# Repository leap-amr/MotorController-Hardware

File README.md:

# MotorController-Hardware
モータドライバのハードウェア設計のためのリポジトリ

# Image

# Development Software Versions
Application: KiCad x64 on x64

Version: 7.0.6, release build

Libraries:
    wxWidgets 3.2.2
    FreeType 2.12.1
    HarfBuzz 6.0.0
    FontConfig 2.14.1
    libcurl/7.88.1-DEV Schannel zlib/1.2.13

Platform: Windows 10 (build 19045), 64-bit edition, 64 bit, Little endian, wxMSW

    Build Info:
    Date: Jul  6 2023 04:56:45
    wxWidgets: 3.2.2 (wchar_t,wx containers)
    Boost: 1.81.0
    OCC: 7.6.3
    Curl: 7.88.1-DEV
    ngspice: 40
    Compiler: Visual C++ 1936 without C++ ABI

Build settings:
    KICAD_SPICE=ON

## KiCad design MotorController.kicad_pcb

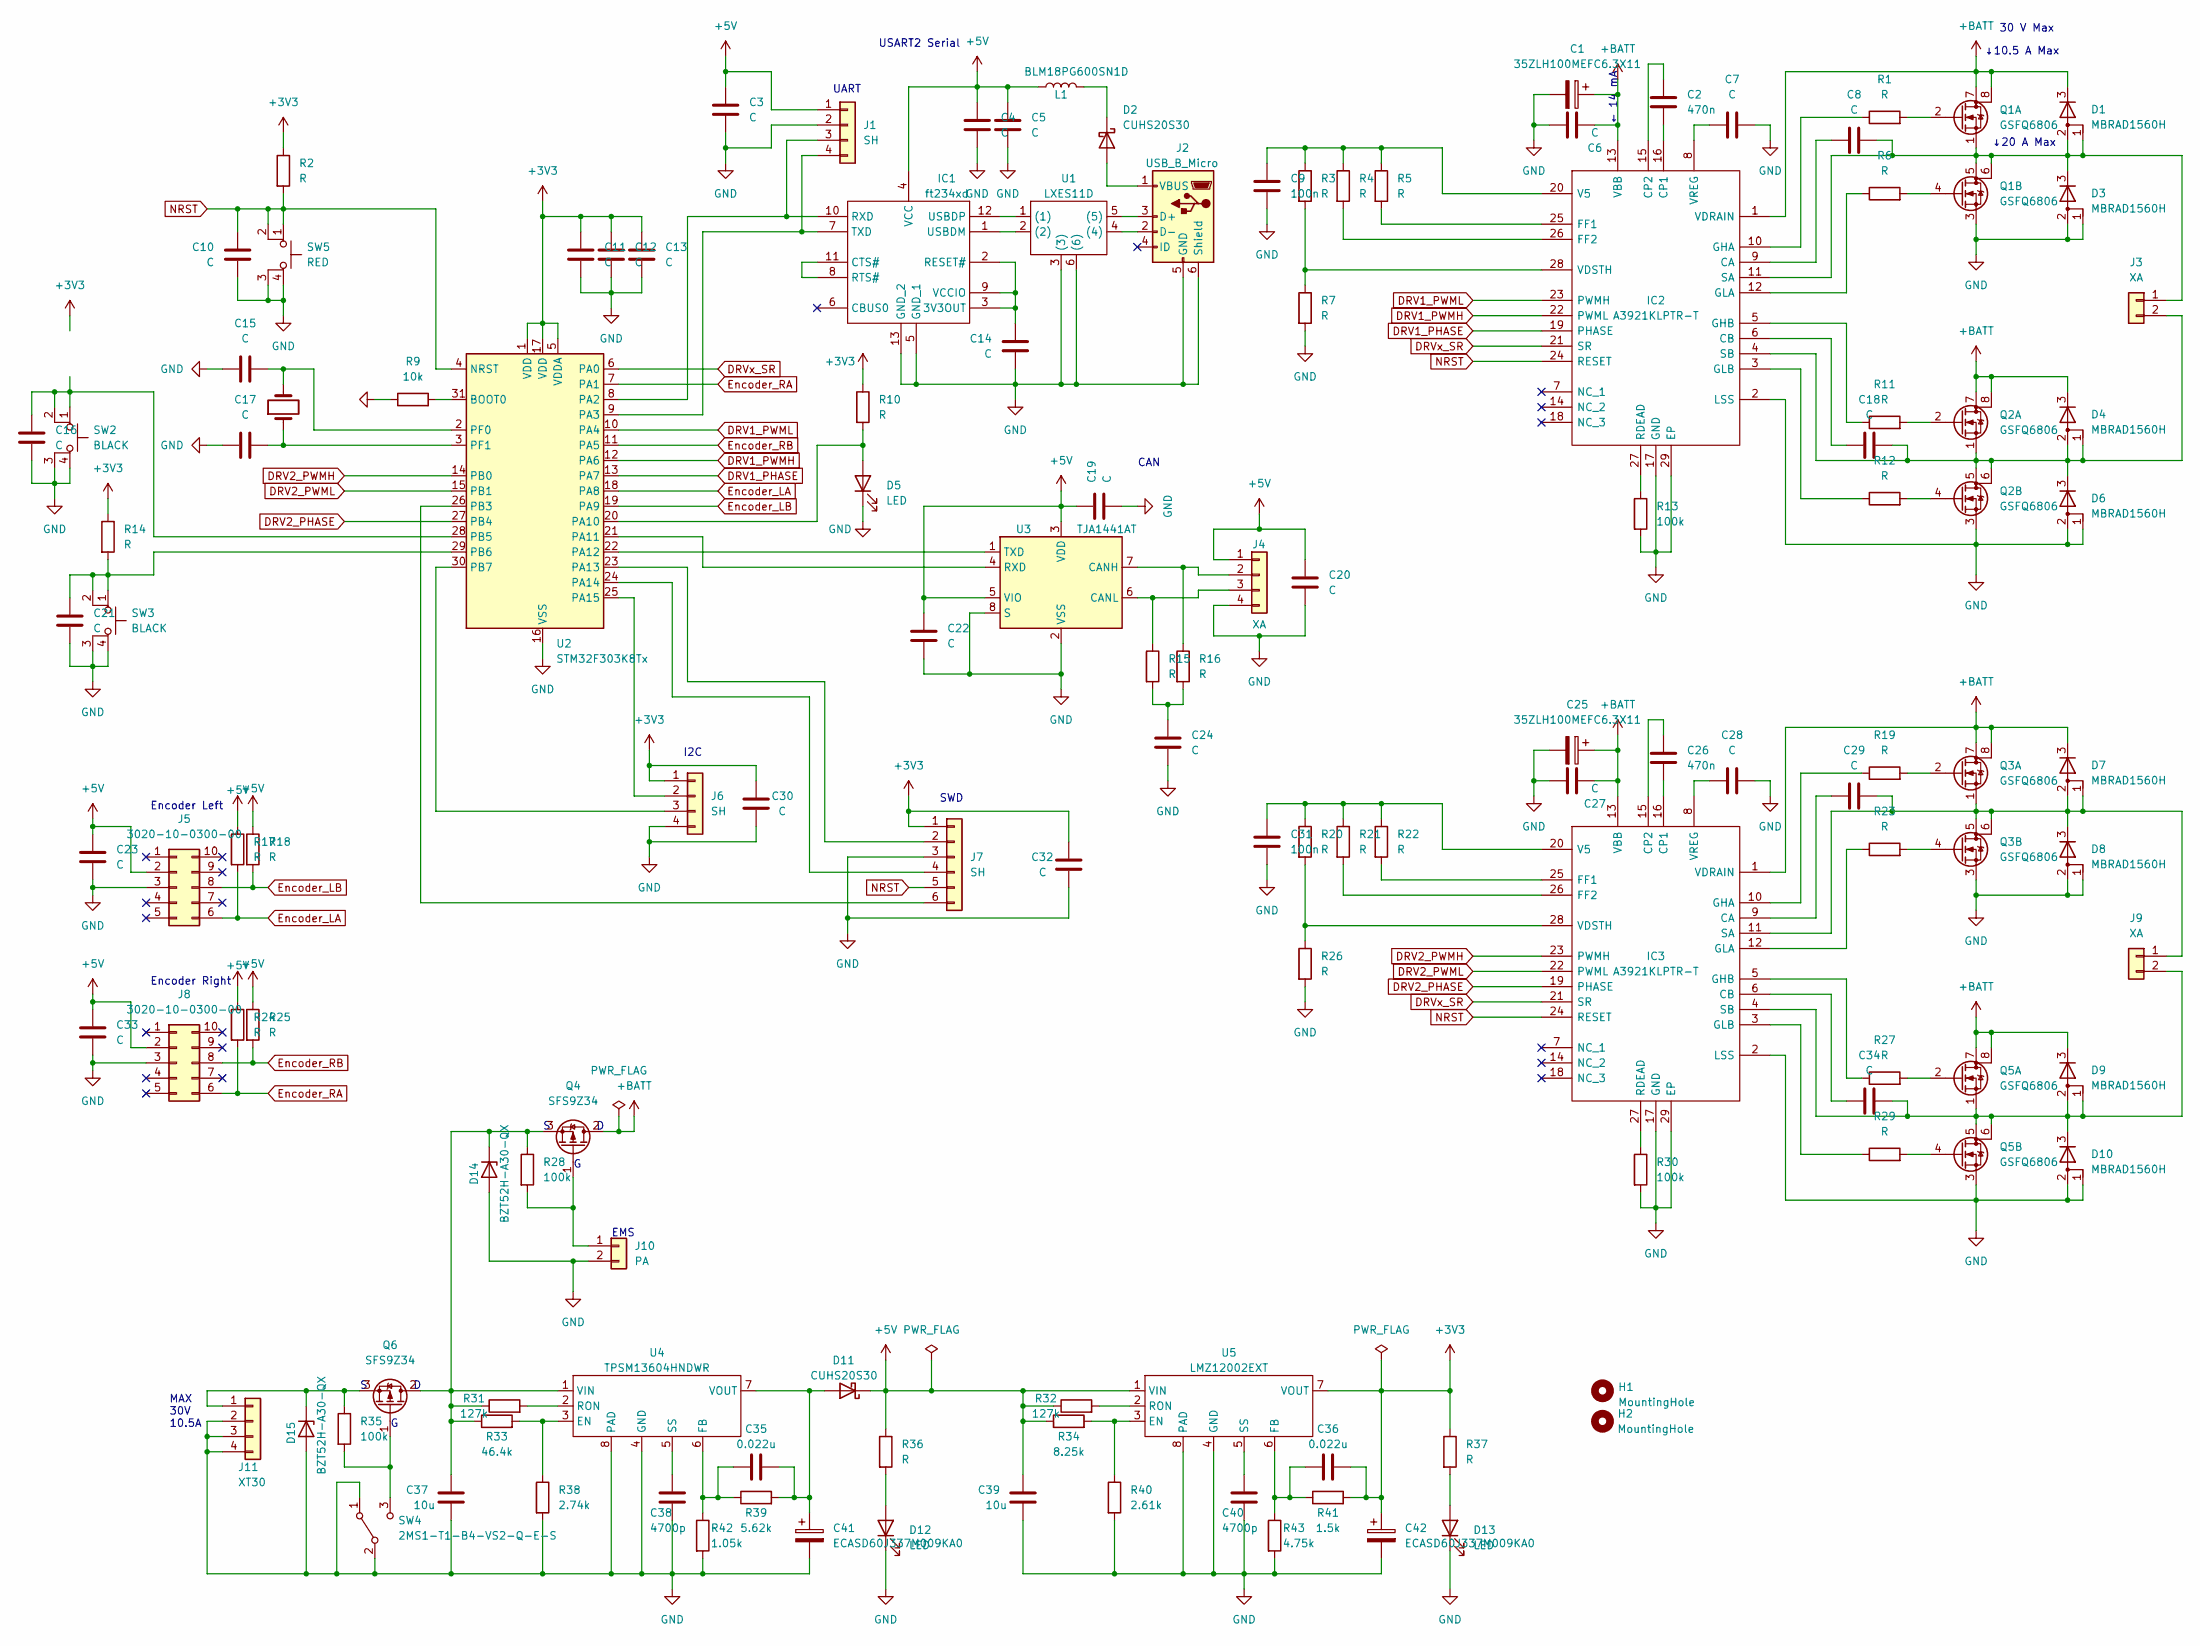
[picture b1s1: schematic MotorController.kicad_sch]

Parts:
C1, C25: 35ZLH100MEFC6.3X11; CP_Radial_D6.3mm_P2.50mm
C2, C26: 470n; C_0603_1608Metric
C3, C4, C5, C6, C7, C8, C10, C11, C12, C13, C14, C15, C16, C17, C18, C19, C20, C21, C22, C23, C24, C27, C28, C29, C30, C32, C33, C34: C; C_0603_1608Metric
C9, C31: 100n; C_0603_1608Metric
C35, C36: 0.022u; C_0603_1608Metric
C37, C39: 10u; C_0603_1608Metric
C38, C40: 4700p; C_0603_1608Metric
C41, C42: ECASD60J337M009KA0; CAPPM7343X310N
D1, D3, D4, D6, D7, D8, D9, D10: MBRAD1560H; DIO_MBRAD1560H
D2, D11: CUHS20S30; CUHS20S40H3F
D5, D12, D13: LED; LED_0603_1608Metric
D14, D15: BZT52H-A30-QX; D_1206_3216Metric
H1, H2: MountingHole; MountingHole_3.2mm_M3
IC1: ft234xd; SON45P300X300X80-13N-D; Manufacturer_Part_Number ft234xd
IC2, IC3: A3921KLPTR-T; A3944KLPTRT; Manufacturer_Part_Number A3921KLPTR-T; Mouser Part Number 250-A3921KLPTR-T
J1, J6: SH; JST_SH_BM04B-SRSS-TB_1x04-1MP_P1.00mm_Vertical
J2: USB_B_Micro; USB_Micro-B_Amphenol_10118194_Horizontal
J3, J9: XA; JST_XA_B02B-XASK-1-A_1x02_P2.50mm_Vertical
J4: XA; JST_XA_B04B-XASK-1-A_1x04_P2.50mm_Vertical
J5, J8: 3020-10-0300-00; IDC-Header_2x05_P2.54mm_Vertical
J7: SH; JST_SH_BM06B-SRSS-TB_1x06-1MP_P1.00mm_Vertical
J10: PA; PA_01x02
J11: XT30; XT30PWM
L1: BLM18PG600SN1D; L_0603_1608Metric
Q1, Q2, Q3, Q5: GSFQ6806; SO-8_3.9x4.9mm_P1.27mm
Q4, Q6: SFS9Z34; TO-220F-3_Horizontal_TabDown
R1, R2, R3, R4, R5, R6, R7, R10, R11, R12, R14, R15, R16, R17, R18, R19, R20, R21, R22, R23, R24, R25, R26, R27, R29, R36, R37: R; R_0603_1608Metric
R9: 10k; R_0603_1608Metric
R13, R28, R30, R35: 100k; R_0603_1608Metric
R31, R32: 127k; R_0603_1608Metric
R33: 46.4k; R_0603_1608Metric
R34: 8.25k; R_0603_1608Metric
R38: 2.74k; R_0603_1608Metric
R39: 5.62k; R_0603_1608Metric
R40: 2.61k; R_0603_1608Metric
R41: 1.5k; R_0603_1608Metric
R42: 1.05k; R_0603_1608Metric
R43: 4.75k; R_0603_1608Metric
SW2, SW3: BLACK; DTS-63-N-V-BLK(TS-0606-F-N
SW4: 2MS1-T1-B4-VS2-Q-E-S
SW5: RED; DTS-63-N-V-BLK(TS-0606-F-N
U1: LXES11D; LXES11DAA2135
U2: STM32F303K8Tx; LQFP-32_7x7mm_P0.8mm
U3: TJA1441AT; SOIC-8_3.9x4.9mm_P1.27mm
U4: TPSM13604HNDWR; Texas_NDW-7_TabPin8
U5: LMZ12002EXT; Texas_NDW-7_TabPin8
Y1: 32M; Crystal_HC49-4H_Vertical

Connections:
+3V3: C11.1, C12.1, C13.1, C30.1, C32.1, C36.2, C42.1, J6.1, J7.1, R2.1, R10.1, R14.1, R37.1, R41.2, U2.1 (VDD), U2.5 (VDDA), U2.17 (VDD), U5.7 (VOUT); also elsewhere on the board
+5V: C3.1, C4.1, C5.1, C19.1, C20.1, C22.1, C23.1, C33.1, C39.1, D11.1 (K), IC1.4 (VCC), J1.1, J4.1, J5.2, J8.2, L1.1, R17.1, R18.1, R24.1, R25.1, R32.1, R34.1, R36.1, U3.3 (VDD), U3.5 (VIO), U5.1 (VIN)
+BATT: C1.1, C6.2, C25.1, C27.2, D1.3 (K), D4.3 (K), D7.3 (K), D9.3 (K), IC2.1 (VDRAIN), IC2.13 (VBB), IC3.1 (VDRAIN), IC3.13 (VBB), Q1.7 (D), Q1.8 (D), Q2.7 (D), Q2.8 (D), Q3.7 (D), Q3.8 (D), Q4.2 (D), Q5.7 (D), Q5.8 (D)
DRV1_PHASE: IC2.19 (PHASE), U2.13 (PA7)
DRV1_PWMH: IC2.22 (PWML), U2.12 (PA6)
DRV1_PWML: IC2.23 (PWMH), U2.10 (PA4)
DRV2_PHASE: IC3.19 (PHASE), U2.27 (PB4)
DRV2_PWMH: IC3.23 (PWMH), U2.14 (PB0)
DRV2_PWML: IC3.22 (PWML), U2.15 (PB1)
DRVx_SR: IC2.21 (SR), IC3.21 (SR), U2.6 (PA0)
Encoder_LA: J5.6, R17.2, U2.18 (PA8)
Encoder_LB: J5.8, R18.2, U2.19 (PA9)
Encoder_RA: J8.6, R24.2, U2.7 (PA1)
Encoder_RB: J8.8, R25.2, U2.11 (PA5)
GND: C1.2, C3.2, C4.2, C5.2, C6.1, C7.2, C9.2, C10.2, C11.2, C12.2, C13.2, C14.2, C15.1, C16.2, C17.1, C19.2, C20.2, C21.2, C22.2, C23.2, C24.2, C25.2, C27.1, C28.2, C30.2, C31.2, C32.2, C33.2, C37.2, C38.2, C39.2, C40.2, C41.2, C42.2, D3.1 (A), D3.2 (A), D5.1 (K), D6.1 (A), D6.2 (A), D8.1 (A), D8.2 (A), D10.1 (A), D10.2 (A), D12.1 (K), D13.1 (K), D14.2 (A), D15.2 (A), IC1.5 (GND_1), IC1.13 (GND_2), IC2.2 (LSS), IC2.17 (GND), IC2.29 (EP), IC3.2 (LSS), IC3.17 (GND), IC3.29 (EP), J1.2, J2.5 (GND), J2.6 (Shield), J4.4, J5.3, J6.4, J7.3, J8.3, J10.2, J11.2, J11.3, J11.4, Q1.3 (S), Q2.3 (S), Q3.3 (S), Q5.3 (S), R7.2, R9.1, R13.2, R26.2, R30.2, R38.2, R40.2, R42.2, R43.2, SW2.3 (K), SW2.4 (A), SW3.3 (K), SW3.4 (A), SW4.1 (A), SW4.2 (B), SW5.3 (K), SW5.4 (A), U1.3 ((3)), U1.6 ((6)), U2.16 (VSS), U2.32 (VSS), U3.2 (VSS), U3.8 (S), U4.4 (GND), U4.8 (PAD), U5.4 (GND), U5.8 (PAD)
NRST: C10.1, IC2.24 (RESET), IC3.24 (RESET), J7.5, R2.2, SW5.1, SW5.2, U2.4 (NRST)
unnamed: C24.1, R15.2, R16.2
unnamed: D2.2 (A), J2.1 (VBUS)
unnamed: D2.1 (K), L1.2
unnamed: C8.1, D1.1 (A), D1.2 (A), D3.3 (K), IC2.11 (SA), J3.1, Q1.1 (S), Q1.5 (D), Q1.6 (D)
unnamed: D5.2 (A), R10.2, U2.20 (PA10)
unnamed: C18.1, D4.1 (A), D4.2 (A), D6.3 (K), IC2.4 (SB), J3.2, Q2.1 (S), Q2.5 (D), Q2.6 (D)
unnamed: C29.1, D7.1 (A), D7.2 (A), D8.3 (K), IC3.11 (SA), J9.1, Q3.1 (S), Q3.5 (D), Q3.6 (D)
unnamed: C34.1, D9.1 (A), D9.2 (A), D10.3 (K), IC3.4 (SB), J9.2, Q5.1 (S), Q5.5 (D), Q5.6 (D)
unnamed: C35.2, C41.1, D11.2 (A), R39.2, U4.7 (VOUT)
unnamed: D12.2 (A), R36.2
unnamed: D13.2 (A), R37.2
unnamed: C37.1, D14.1 (K), Q4.3 (S), Q6.2 (D), R28.1, R31.1, R33.1, U4.1 (VIN)
unnamed: D15.1 (K), J11.1, Q6.3 (S), R35.1
unnamed: C14.1, IC1.2 (RESET#), IC1.3 (3V3OUT), IC1.9 (VCCIO)
unnamed: IC1.8 (RTS#), IC1.11 (CTS#)
unnamed: IC1.10 (RXD), J1.3, U2.8 (PA2)
unnamed: IC1.7 (TXD), J1.4, U2.9 (PA3)
unnamed: IC1.1 (USBDM), U1.2 ((2))
unnamed: IC1.12 (USBDP), U1.1 ((1))
unnamed: C8.2, IC2.9 (CA)
unnamed: C18.2, IC2.6 (CB)
unnamed: C2.1, IC2.16 (CP1)
unnamed: C2.2, IC2.15 (CP2)
unnamed: IC2.25 (FF1), R5.2
unnamed: IC2.26 (FF2), R4.2
unnamed: IC2.10 (GHA), R1.1
unnamed: IC2.5 (GHB), R11.1
unnamed: IC2.12 (GLA), R6.1
unnamed: IC2.3 (GLB), R12.1
unnamed: IC2.27 (RDEAD), R13.1
unnamed: C9.1, IC2.20 (V5), R3.1, R4.1, R5.1
unnamed: IC2.28 (VDSTH), R3.2, R7.1
unnamed: C7.1, IC2.8 (VREG)
unnamed: C29.2, IC3.9 (CA)
unnamed: C34.2, IC3.6 (CB)
unnamed: C26.1, IC3.16 (CP1)
unnamed: C26.2, IC3.15 (CP2)
unnamed: IC3.25 (FF1), R22.2
unnamed: IC3.26 (FF2), R21.2
unnamed: IC3.10 (GHA), R19.1
unnamed: IC3.5 (GHB), R27.1
unnamed: IC3.12 (GLA), R23.1
unnamed: IC3.3 (GLB), R29.1
unnamed: IC3.27 (RDEAD), R30.1
unnamed: C31.1, IC3.20 (V5), R20.1, R21.1, R22.1
unnamed: IC3.28 (VDSTH), R20.2, R26.1
unnamed: C28.1, IC3.8 (VREG)
unnamed: J2.3 (D+), U1.5 ((5))
unnamed: J2.2 (D-), U1.4 ((4))
unnamed: J4.2, R16.1, U3.7 (CANH)
unnamed: J4.3, R15.1, U3.6 (CANL)
unnamed: J6.2, U2.25 (PA15)
unnamed: J6.3, U2.30 (PB7)
unnamed: J7.2, U2.23 (PA13)
unnamed: J7.4, U2.24 (PA14)
unnamed: J7.6, U2.26 (PB3)
unnamed: J10.1, Q4.1 (G), R28.2
unnamed: Q1.2 (G), R1.2
unnamed: Q1.4 (G), R6.2
unnamed: Q2.2 (G), R11.2
unnamed: Q2.4 (G), R12.2
unnamed: Q3.2 (G), R19.2
unnamed: Q3.4 (G), R23.2
unnamed: Q5.2 (G), R27.2
unnamed: Q5.4 (G), R29.2
unnamed: Q6.1 (G), R35.2, SW4.3 (C)
unnamed: R9.2, U2.31 (BOOT0)
unnamed: U2.21 (PA11), U3.4 (RXD)
unnamed: U2.22 (PA12), U3.1 (TXD)
unnamed 85: C16.1, SW2.1, SW2.2, U2.28 (PB5); also elsewhere on the board
unnamed: C21.1, R14.2, SW3.1, SW3.2, U2.29 (PB6)
unnamed: C15.2, U2.2 (PF0), Y1.2
unnamed: C17.2, U2.3 (PF1), Y1.1
unnamed: R33.2, R38.1, U4.3 (EN)
unnamed: C35.1, R39.1, R42.1, U4.6 (FB)
unnamed: R31.2, U4.2 (RON)
unnamed: C38.1, U4.5 (SS)
unnamed: R34.2, R40.1, U5.3 (EN)
unnamed: C36.1, R41.1, R43.1, U5.6 (FB)
unnamed: R32.2, U5.2 (RON)
unnamed: C40.1, U5.5 (SS)

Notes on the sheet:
Encoder Right
USART2 Serial
↓20 A Max
UART
MAX 30V 10.5A
CAN
↓10.5 A Max
I2C
← 14 mA
SWD
Encoder Left
EMS
30 V Max

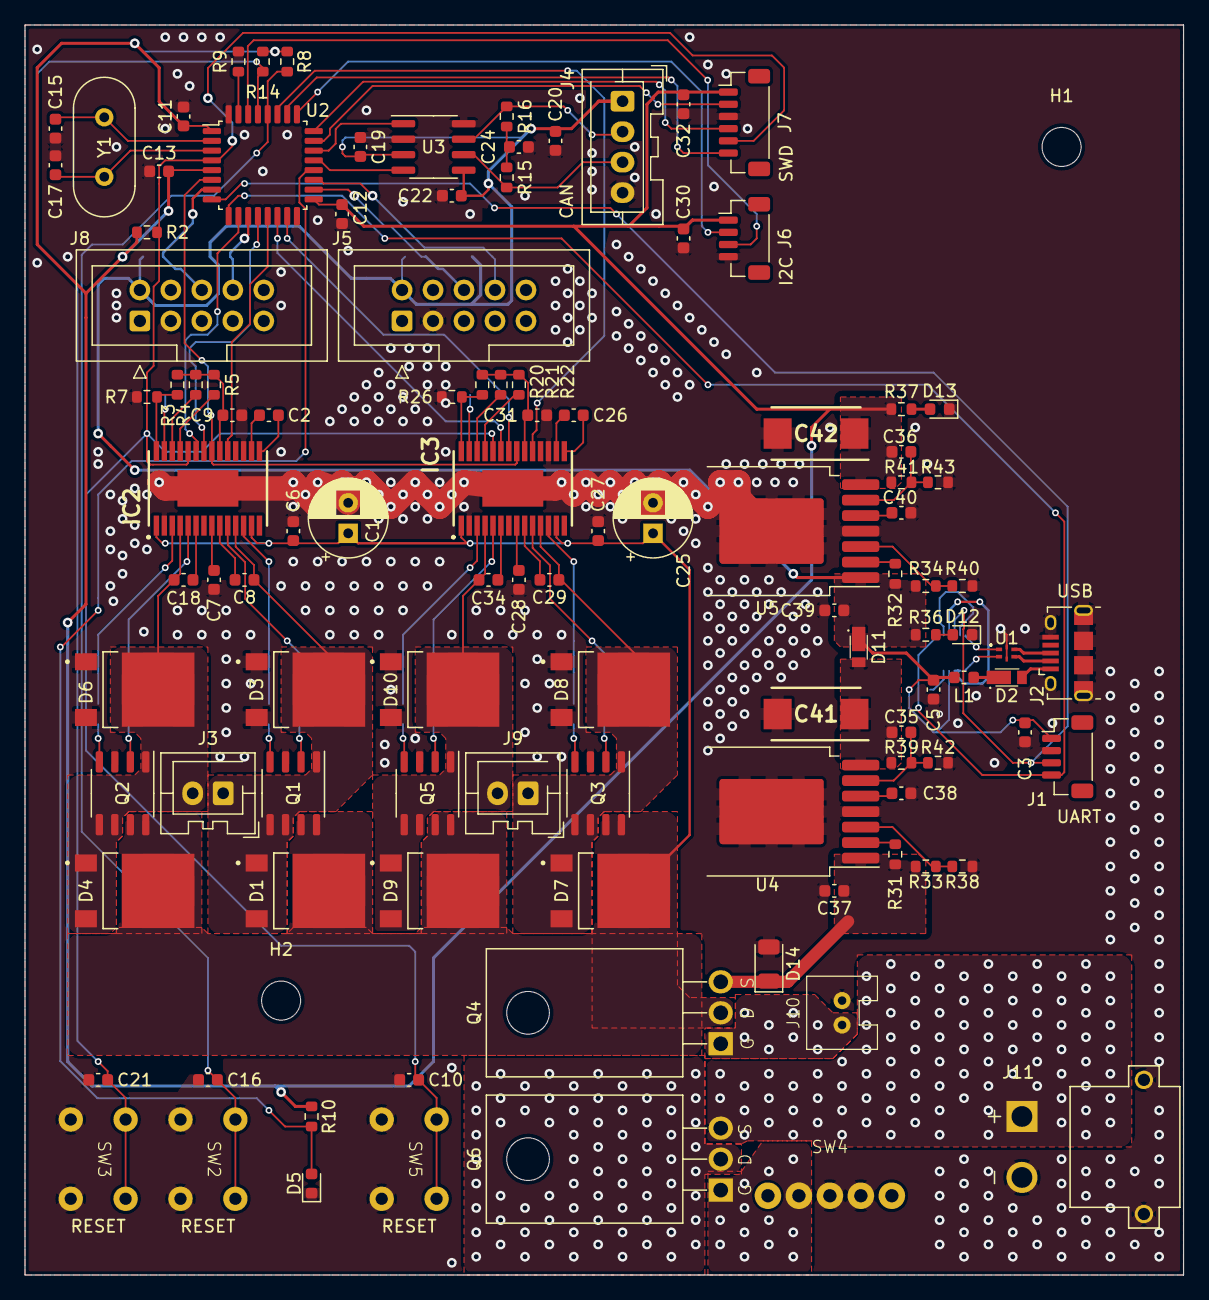
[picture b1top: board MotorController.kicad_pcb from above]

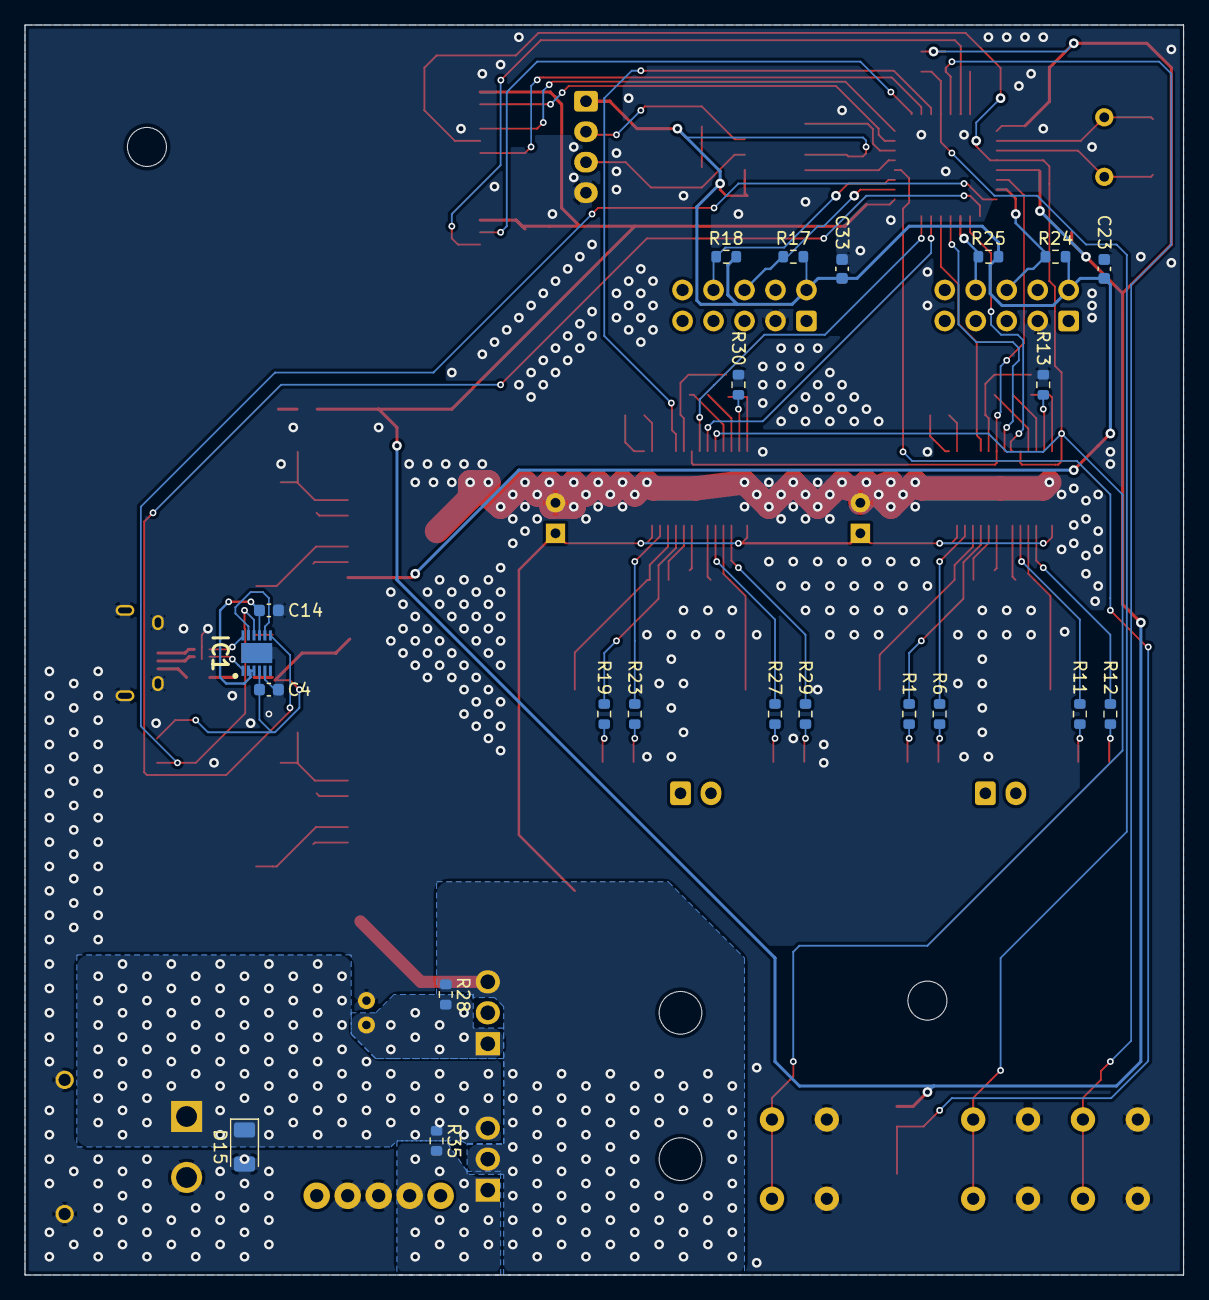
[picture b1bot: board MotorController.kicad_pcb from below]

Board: 2 copper layers, 95.0 x 102.5 mm, 133 parts (22 on the bottom side), 97 nets.

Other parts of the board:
R8: R; R_0603_1608Metric

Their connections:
+3V3: R8.1; also elsewhere on the board
unnamed 85: R8.2; also elsewhere on the board

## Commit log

2023-07-07 create issue template
2023-08-21 でーきたー！30% の完成度の回路図！CAN 通信用の回路は置きっぱなし
2023-08-21 CAN 通信周りの端子の変更と電源スイッチの回路図を変更
2023-08-21 PDF を追加
2023-08-21 れどめに KiCAD の情報干せた
2023-08-22 とりあえずコミット
2023-09-01 先輩に見せるためにいったんコミット。コネクタの回路図とか変えた
2023-09-01 PDF を更新
2023-09-08 A3921 の回路を訂正・USB 5V から DCDC 5V に入り込まないようにした・IC1 にパスコン追加
2023-09-08 hoge
2023-09-08 緊急停止スイッチをマイコンではなくゲートドライバにつなげた
2023-09-08 PDF の更新
2023-09-09 緊急停止スイッチがプッシュオフであることに気が付いてそれを修正
2023-09-09 bak ディレクトリを削除
2023-09-09 コネクタの形状を記しておいた。余ったピンで CAN トランシーバ使えるようにした。ERC 通した。PDF も更新した
2023-09-15 power flag の指定方法を変えた。+BATT の位置を Pch FET の前に置いた
2023-10-09 DCDC の出力コンデンサの記号を有極性にした。H ブリッジ FET にダイオード外付けした。A3921 のリセットピンと CPU のリセットピンを共有した。安全停止をモータの電力供給の手前に追加した。安全停止を Pch FET で実現しようとした。Pch FET の型番決めた
2023-10-09 フットプリントの更新
2023-10-09 フットプリント再更新
2023-10-09 pdf 更新
2023-10-14 追加パーツ含めてアノテーション全部終わらせた。フットプリントをグループごとに分類して分けて設置した
2023-10-27 電源回路設置完了！USB の回路設置中
2023-11-25 Update issue templates
2023-11-25 USB 周りの配線を少し進めた
2023-11-30 Z 実装
2023-11-30 remove swp file
2023-12-04 CPU CAN MD DCDC の位置感決めた あとは UI
2023-12-13 一旦 push
2023-12-16 GND ベタを塗る直前までやった
2024-01-11 GND 以外の配線をとりあえずやった。水晶の下の配線をなくした。パーツ同士の干渉をなくした。
2024-01-12 GND アンテナ配線除去中（ビア最大サイズ 0.5 で穴だらけ
2024-01-12 size 1 drill 0.5 to size 0.8 drill 0.4
2024-01-12 DRC 通してシルク以外のエラーを修正
2024-01-12 画像と PDF の更新
